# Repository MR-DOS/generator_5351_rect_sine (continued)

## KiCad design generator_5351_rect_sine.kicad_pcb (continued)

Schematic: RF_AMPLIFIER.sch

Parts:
C601, C606, C607, C609, C615: 100p; C_0805_2012Metric_Pad1.33x1.40mm_HandSolder
C602, C603, C604, C605, C608, C610, C611, C612, C614, C619: 10n; C_0805_2012Metric_Pad1.33x1.40mm_HandSolder
C613, C616, C617: 100n; C_0805_2012Metric_Pad1.33x1.40mm_HandSolder
C618, C620: 1n; C_0805_2012Metric_Pad1.33x1.40mm_HandSolder
L601: 1u; L_0805_2012Metric_Pad1.33x1.40mm_HandSolder
Q601, Q602, Q603, Q604, Q605, Q606, Q607, Q608, Q609, Q610, Q611, Q612: 2SC5773; SC-59_Handsoldering
Q613, Q614, Q615, Q616: BC817; SOT-23_Handsoldering
R601, R603: 15k; R_0805_2012Metric_Pad1.33x1.40mm_HandSolder
R602: 3.3; R_0805_2012Metric_Pad1.33x1.40mm_HandSolder
R604, R605: 22; R_0805_2012Metric_Pad1.33x1.40mm_HandSolder
R606, R607: 0R; R_0805_2012Metric_Pad1.33x1.40mm_HandSolder
R608, R609: 3k3; R_0805_2012Metric_Pad1.33x1.40mm_HandSolder
R610: 2k2; R_0805_2012Metric_Pad1.33x1.40mm_HandSolder
R611, R622, R623: 10; R_0805_2012Metric_Pad1.33x1.40mm_HandSolder
R612, R620: 330; R_0805_2012Metric_Pad1.33x1.40mm_HandSolder
R613, R616, R617: 1k5; R_0805_2012Metric_Pad1.33x1.40mm_HandSolder
R614, R615: 47; R_0805_2012Metric_Pad1.33x1.40mm_HandSolder
R618, R619: 15; R_0805_2012Metric_Pad1.33x1.40mm_HandSolder
R621: 47k; R_0805_2012Metric_Pad1.33x1.40mm_HandSolder
R624, R625, R627, R628: 470; R_0805_2012Metric_Pad1.33x1.40mm_HandSolder
R626: 68k; R_0805_2012Metric_Pad1.33x1.40mm_HandSolder
T601: TC-1T+; AT224-1A
U601, U602: NE612; SO-8_5.3x6.2mm_P1.27mm

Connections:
+5V: C601.1, C602.1, Q601.3, Q602.3, R610.2, R617.1, R622.1, R623.1, T601.2 (SC); also elsewhere on the board
/ANALOG/GAIN1: R621.1; also elsewhere on the board
/ANALOG/GAIN2: R626.1; also elsewhere on the board
/ANALOG/HF_Switch_3/OUT: T601.4 (AB); also elsewhere on the board
/ANALOG/RF_AMPLIFIER/BUFFER_BIAS: C605.1, C606.1, C607.1, Q605.1, Q605.3, Q606.1, Q607.1, Q608.1, Q609.1, R610.1
/ANALOG/RF_AMPLIFIER/GAIN_A: C603.1, Q603.2, Q610.3, R611.2
/ANALOG/RF_AMPLIFIER/GAIN_B: C604.1, Q604.2, Q611.3, R611.1
/ANALOG/RF_AMPLIFIER/IN: C613.1; also elsewhere on the board
/ANALOG/RF_AMPLIFIER/NE612_A: Q601.1, R608.1, U602.4 (OUT_A)
/ANALOG/RF_AMPLIFIER/NE612_B: Q602.1, R609.1, U602.5 (OUT_B)
/ANALOG/RF_AMPLIFIER/RF_GAIN_SWITCH_1/A: R602.1; also elsewhere on the board
/ANALOG/RF_AMPLIFIER/RF_GAIN_SWITCH_1/OUT: C603.2, R601.2; also elsewhere on the board
/ANALOG/RF_AMPLIFIER/RF_GAIN_SWITCH_2/A: R602.2; also elsewhere on the board
/ANALOG/RF_AMPLIFIER/RF_GAIN_SWITCH_2/OUT: C604.2, R603.1; also elsewhere on the board
unnamed: C608.1, C609.1, R622.2, U601.8 (VCC)
unnamed: C610.1, Q610.1, Q611.1, Q612.1, Q612.3, R617.2
unnamed: C611.1, Q614.3 (C), U601.1 (IN_A)
unnamed: C612.1, U601.2 (IN_B)
unnamed: C613.2, U601.6 (OSC_B)
unnamed: C614.1, C615.1, R623.2, U602.8 (VCC)
unnamed: C616.1, U602.2 (IN_B)
unnamed: C616.2, U601.4 (OUT_A)
unnamed: C617.1, U602.1 (IN_A)
unnamed: C617.2, U601.5 (OUT_B)
unnamed: C618.1, Q613.1 (B), Q613.3 (C), Q614.1 (B), R621.2
unnamed: C619.1, Q616.3 (C), U602.6 (OSC_B)
unnamed: C620.1, Q615.1 (B), Q615.3 (C), Q616.1 (B), R626.2
unnamed: L601.1, R601.1, R603.2
unnamed: Q601.2, R606.1
unnamed: Q602.2, R607.1
unnamed: Q603.1, Q607.3, R606.2
unnamed: Q603.3, R604.2
unnamed: Q604.1, Q608.3, R607.2
unnamed: Q604.3, R605.2
unnamed: Q605.2, R612.1
unnamed: Q606.2, R613.1
unnamed: Q606.3, R608.2
unnamed: Q607.2, R614.1
unnamed: Q608.2, R615.1
unnamed: Q609.2, R616.1
unnamed: Q609.3, R609.2
unnamed: Q610.2, R618.1
unnamed: Q611.2, R619.1
unnamed: Q612.2, R620.1
unnamed: Q613.2 (E), R624.1
unnamed: Q614.2 (E), R625.1
unnamed: Q615.2 (E), R627.1
unnamed: Q616.2 (E), R628.1
unnamed: R604.1, T601.3 (SA)
unnamed: R605.1, T601.1 (SB)
SW_GND: C601.2, C602.2, C605.2, C606.2, C607.2, C608.2, C609.2, C610.2, C611.2, C612.2, C614.2, C615.2, C618.2, C619.2, C620.2, L601.2, R612.2, R613.2, R614.2, R615.2, R616.2, R618.2, R619.2, R620.2, R624.2, R625.2, R627.2, R628.2, T601.6 (AA), U601.3 (GND), U602.3 (GND); also elsewhere on the board

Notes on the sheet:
50uA current sink
35uA current sink
3.32V
2.49V
1.62V
535mV
612mV
1.40V
543mV
458mV
4.23V
Gain select - for high frequencies between 80 and 100 MHz Higher gain causes higher distortion
1.29V
506mV
Under normal circumstances, attach GAIN2 to 3V3 to get full amplification, use the other current sink to set gain.
Discharge path for DC Could use some improvement
HERE goes the gain select circuit

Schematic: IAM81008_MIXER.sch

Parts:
C1001, C1004: 10n; C_0805_2012Metric_Pad1.33x1.40mm_HandSolder
C1002, C1003, C1006, C1007: 1n; C_0805_2012Metric_Pad1.33x1.40mm_HandSolder
C1005: 100p; C_0805_2012Metric_Pad1.33x1.40mm_HandSolder
R1001: 4R7; R_0805_2012Metric_Pad1.33x1.40mm_HandSolder
T1001, T1002: TC-1T+; AT224-1A
U1001: IAM81008; SO-8_5.3x6.2mm_P1.27mm

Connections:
+5V: R1001.1; also elsewhere on the board
/ANALOG/100_MHz_Legendre_LPF_1/IN: C1001.1; also elsewhere on the board
/ANALOG/HF_Switch_1/A: T1001.4 (AB); also elsewhere on the board
/ANALOG/IAM81008_MIXER/IN_A: T1002.6 (AA); also elsewhere on the board
unnamed: C1001.2, U1001.1 (IF_OUT)
unnamed: C1002.1, U1001.4 (RF_IN)
unnamed: C1002.2, T1001.1 (SB)
unnamed: C1003.1, U1001.8 (RF_GND_OPT)
unnamed: C1003.2, T1001.3 (SA)
unnamed: C1004.1, C1005.1, R1001.2, U1001.7 (VCC)
unnamed: C1006.1, U1001.5 (LO_IN)
unnamed: C1006.2, T1002.1 (SB)
unnamed: C1007.1, U1001.6 (LO_GND_OPT)
unnamed: C1007.2, T1002.3 (SA)
SW_GND: C1004.2, C1005.2, T1001.2 (SC), T1001.6 (AA), T1002.2 (SC), T1002.4 (AB), U1001.2 (GND), U1001.3 (GND); also elsewhere on the board

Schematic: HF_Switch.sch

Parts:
C1101: 1n; C_0805_2012Metric_Pad1.33x1.40mm_HandSolder
U1101: PE4259; SOT363(TSSOP6)

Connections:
/ANALOG/BAND_SEL: U1101.4 (CTRL); also elsewhere on the board
/ANALOG/HF_Switch_1/A: U1101.1 (RF1); also elsewhere on the board
/ANALOG/HF_Switch_1/B: U1101.3 (RF2); also elsewhere on the board
/ANALOG/HF_Switch_1/OUT: U1101.5 (RFC); also elsewhere on the board
SW_GND: C1101.2, U1101.2 (GND); also elsewhere on the board

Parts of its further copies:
C701, C801, C1201, C1401, C1501, C1601, C1701: 1n; C_0805_2012Metric_Pad1.33x1.40mm_HandSolder
U701, U801, U1201, U1401, U1501, U1601, U1701: PE4259; SOT363(TSSOP6)

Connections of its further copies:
/ANALOG/ATTENUATOR/IN: U1601.5 (RFC); also elsewhere on the board
/ANALOG/BAND_SEL: U1201.4 (CTRL), U1401.4 (CTRL), U1501.4 (CTRL); also elsewhere on the board
/ANALOG/GAIN_SELECT: U701.4 (CTRL), U801.4 (CTRL); also elsewhere on the board
/ANALOG/HF_Switch_1/B: U1201.3 (RF2); also elsewhere on the board
/ANALOG/HF_Switch_3/A: U1401.1 (RF1); also elsewhere on the board
/ANALOG/HF_Switch_3/B: U1401.3 (RF2); also elsewhere on the board
/ANALOG/HF_Switch_3/OUT: U1401.5 (RFC); also elsewhere on the board
/ANALOG/HF_Switch_5/A: U1601.1 (RF1); also elsewhere on the board
/ANALOG/HF_Switch_5/B: U1501.5 (RFC), U1601.3 (RF2)
/ANALOG/HF_Switch_6/A: U1701.1 (RF1); also elsewhere on the board
/ANALOG/HF_Switch_6/B: U1701.3 (RF2); also elsewhere on the board
/ANALOG/HIGH_BAND: U1501.3 (RF2); also elsewhere on the board
/ANALOG/LOW_BAND: U1501.1 (RF1); also elsewhere on the board
/ANALOG/RF_AMPLIFIER/IN: U1201.5 (RFC); also elsewhere on the board
/ANALOG/RF_AMPLIFIER/RF_GAIN_SWITCH_1/A: U701.1 (RF1); also elsewhere on the board
/ANALOG/RF_AMPLIFIER/RF_GAIN_SWITCH_1/B: U701.3 (RF2)
/ANALOG/RF_AMPLIFIER/RF_GAIN_SWITCH_1/OUT: U701.5 (RFC); also elsewhere on the board
/ANALOG/RF_AMPLIFIER/RF_GAIN_SWITCH_2/A: U801.1 (RF1); also elsewhere on the board
/ANALOG/RF_AMPLIFIER/RF_GAIN_SWITCH_2/B: U801.3 (RF2)
/ANALOG/RF_AMPLIFIER/RF_GAIN_SWITCH_2/OUT: U801.5 (RFC); also elsewhere on the board
/ANALOG/SHAPE_SELECT: U1601.4 (CTRL); also elsewhere on the board
/ANALOG/SINE_LOW: U1201.1 (RF1); also elsewhere on the board
/ANALOG/TERMINATION: U1701.4 (CTRL); also elsewhere on the board
/RF_DETECTOR/IN+: U1701.5 (RFC); also elsewhere on the board
SW_GND: C701.2, C801.2, C1201.2, C1401.2, C1501.2, C1601.2, C1701.2, U701.2 (GND), U801.2 (GND), U1201.2 (GND), U1401.2 (GND), U1501.2 (GND), U1601.2 (GND), U1701.2 (GND); also elsewhere on the board

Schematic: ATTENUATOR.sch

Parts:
C1801: 1n; C_0805_2012Metric_Pad1.33x1.40mm_HandSolder
C1802: 100n; C_0805_2012Metric_Pad1.33x1.40mm_HandSolder
R1801, R1802: 10k; R_0805_2012Metric_Pad1.33x1.40mm_HandSolder
U1801: PE4306; QFN-20-1EP_4x4mm_Pitch0.5mm

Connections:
/ANALOG/ATTENUATOR/IN: U1801.2 (RF1); also elsewhere on the board
/ANALOG/ATT_0: R1802.2
/ANALOG/ATT_1: U1801.4 (CLOCK)
/ANALOG/ATT_2: U1801.5 (LE)
/RF_DETECTOR/IN+: U1801.14 (RF2); also elsewhere on the board
unnamed: R1801.1, U1801.1 (C16)
unnamed: R1802.1, U1801.3 (DATA)
SW_GND: C1801.1, C1802.2, R1801.2, U1801.7 (PUP1), U1801.8 (PUP2), U1801.10 (GND), U1801.11 (GND), U1801.12 (Vss/GND), U1801.15 (C8), U1801.16 (C4), U1801.17 (C2), U1801.18 (GND), U1801.19 (C1), U1801.20 (N/C), U1801.21 (GND_PAD); also elsewhere on the board

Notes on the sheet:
The 10k resistors serve as a protection against "package resonance". Awful.

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
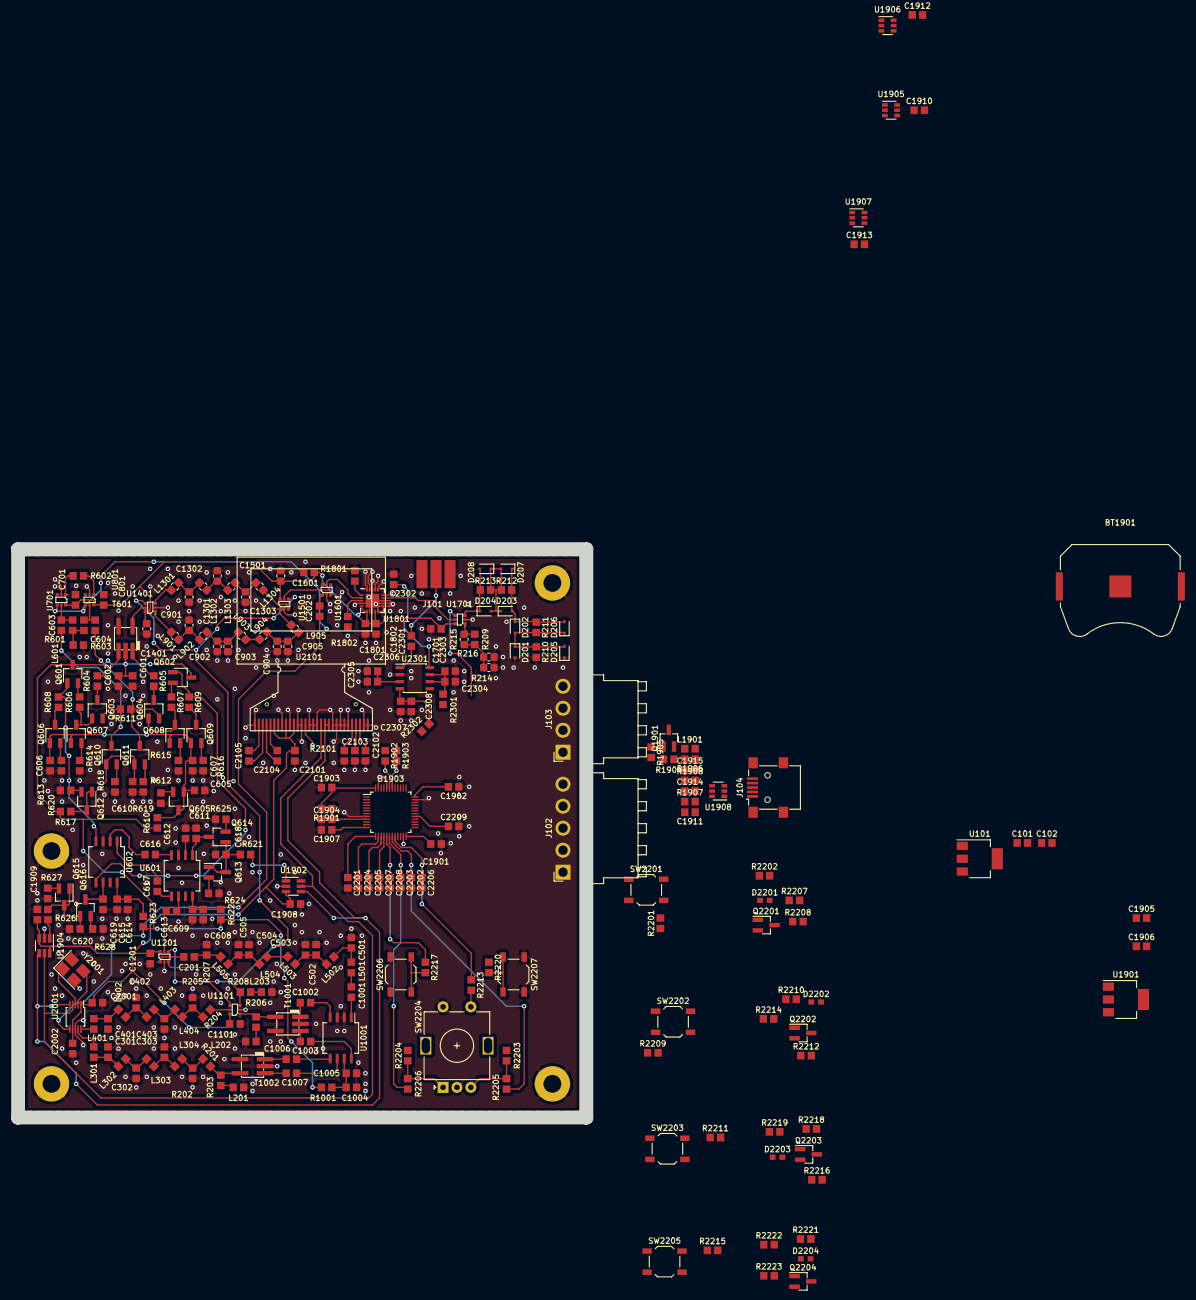
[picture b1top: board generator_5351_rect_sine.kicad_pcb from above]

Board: 2 copper layers, 102.4 x 102.4 mm, 284 parts (0 on the bottom side), 191 nets.

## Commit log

2021-11-23 Create LICENSE
    Added GPLv3 license
